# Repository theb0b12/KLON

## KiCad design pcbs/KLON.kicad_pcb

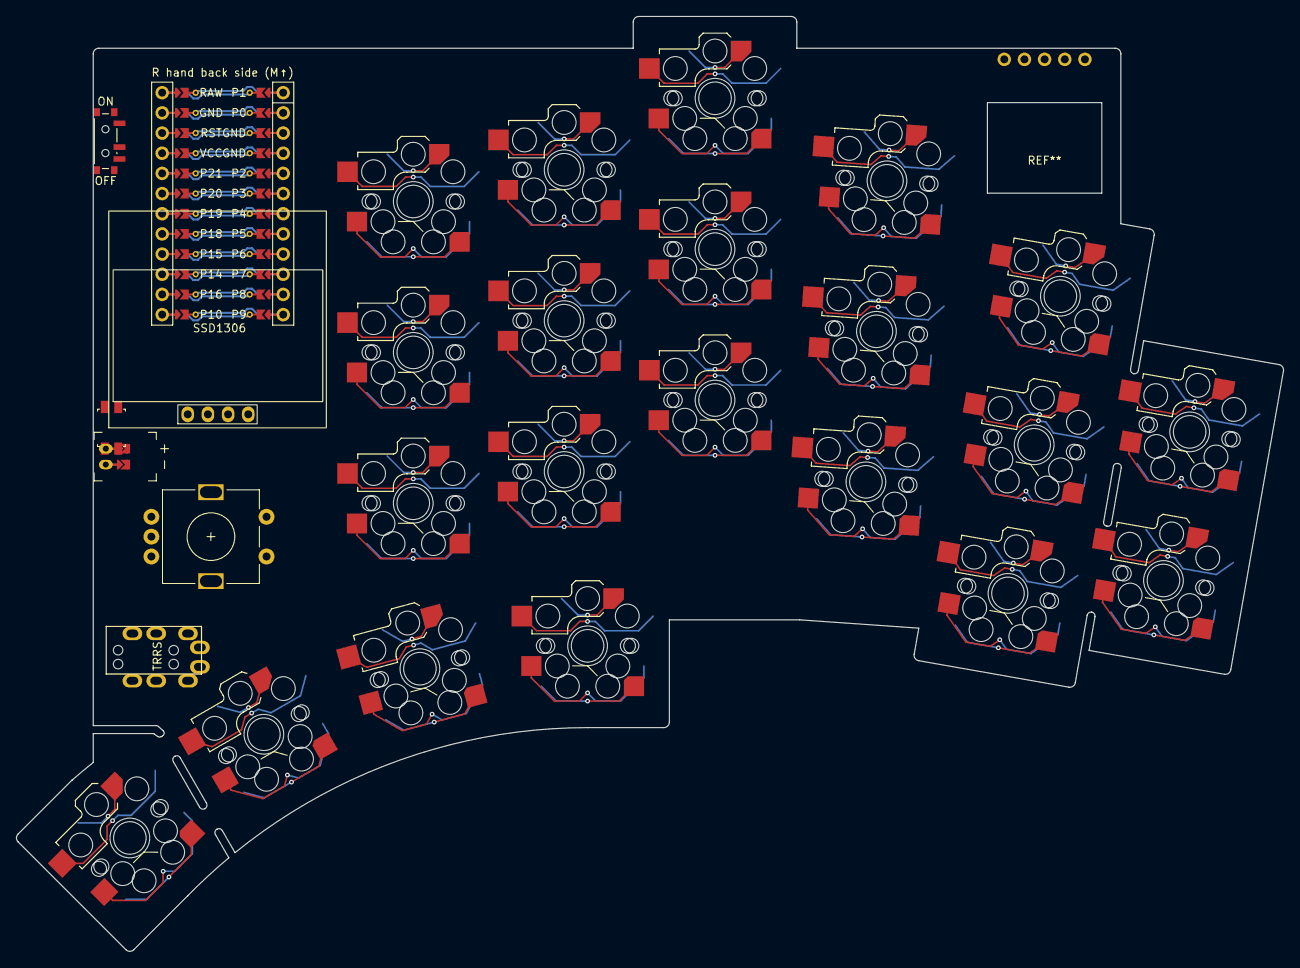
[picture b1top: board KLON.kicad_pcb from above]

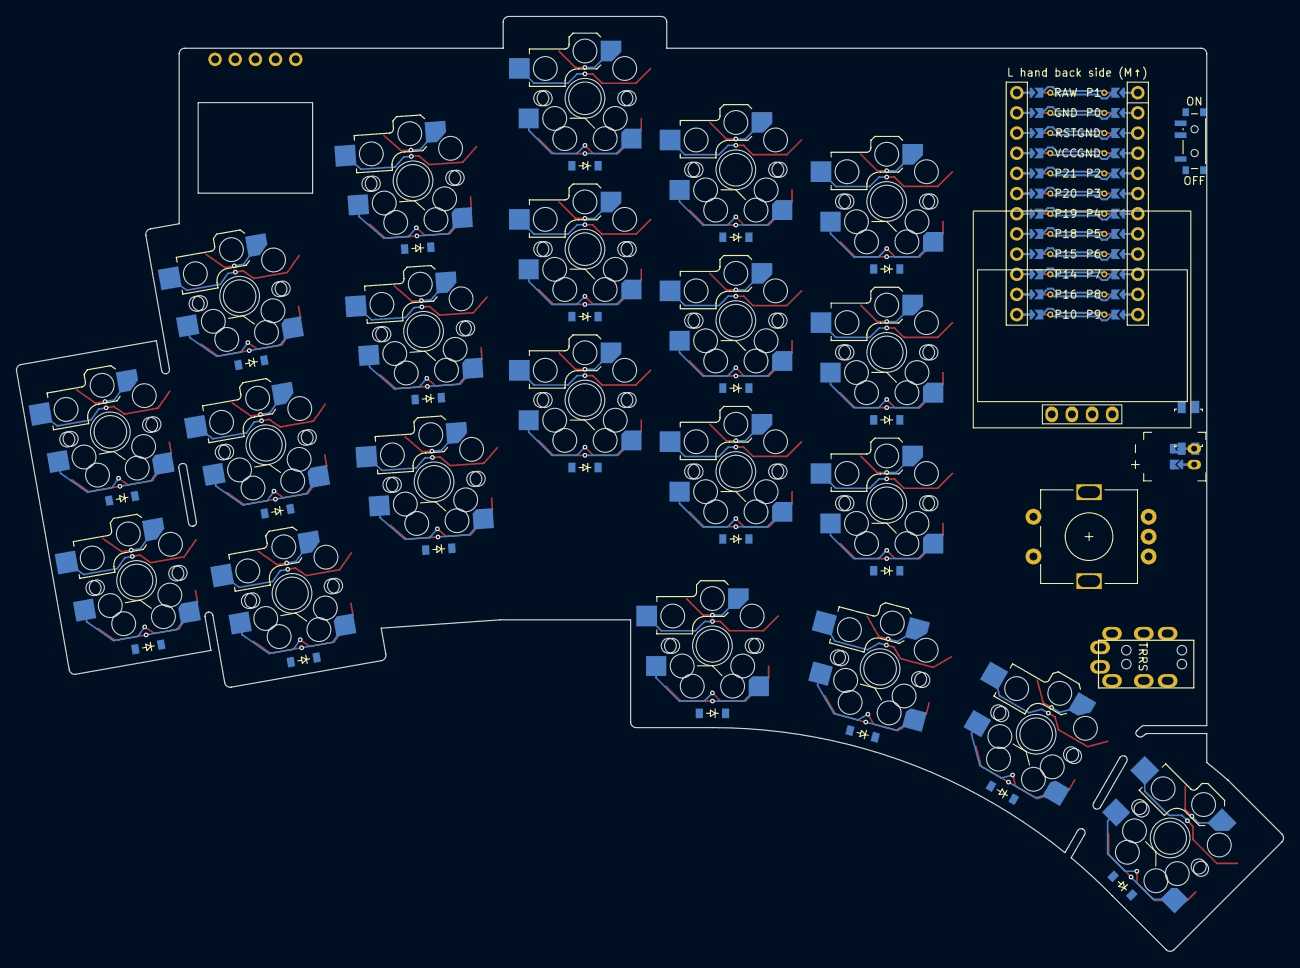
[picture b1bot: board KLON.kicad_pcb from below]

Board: 2 copper layers, 159.6 x 117.7 mm, 71 parts (63 on the bottom side), 29 nets.

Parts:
D1, D2, D3, D4, D5, D6, D7, D8, D9, D10, D11, D12, D13, D14, D15, D16, D17, D18, D19, D20, D21: diode_tht_sod123
JST1: battery_connector_jst_ph_2
MCU1: mcu_nice_nano
PWR1: power_switch_smd_side
RST1: reset_switch_smd_side
S1, S2, S3, S4, S5, S6, S7, S8, S9, S10, S11, S12, S13, S14, S15, S16, S17, S18, S19, S20, S21: switch_choc_v1_v2
S22, S23, S24, S25, S26, S27, S28, S29, S30, S31, S32, S33, S34, S35, S36, S37, S38, S39, S40, S41, S42: switch_mx
XX1: Pimoroni Haptic Buzz DRV2605L Driver
XX2: RotaryEncoder_Alps_EC11E-Switch_Vertical_H20mm-keebio_modif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
XX3: SSD1306_128x64OLED
XX4: MJ-4PP-9

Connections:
1_r0: D18.2, S18.2, S39.2
2_r0: D19.2, S19.2, S40.2
3_r0: D20.2, S20.2, S41.2
4_r0: D21.2, S21.2, S42.2
BAT_P: JST1.1, PWR1.1, PWR1.3
GND: JST1.2, MCU1.103, MCU1.104, MCU1.123, RST1.1, RST1.3
JST1_1: JST1.11, JST1.21, JST1.31
JST1_2: JST1.12, JST1.22, JST1.32
RAW: MCU1.124, PWR1.2
RST: MCU1.122, RST1.2, RST1.4
idk: XX2.A, XX2.B, XX2.C, XX2.MP, XX2.S1, XX2.S2
index_bottom: D4.2, S4.2, S25.2
index_home: D5.2, S5.2, S26.2
index_top: D6.2, S6.2, S27.2
inner_bottom: D1.2, S1.2, S22.2
inner_home: D2.2, S2.2, S23.2
inner_top: D3.2, S3.2, S24.2
middle_bottom: D7.2, S7.2, S28.2
middle_home: D8.2, S8.2, S29.2
middle_top: D9.2, S9.2, S30.2
pinky_bottom: D13.2, S13.2, S34.2
pinky_extra_bottom: D16.2, S16.2, S37.2
pinky_extra_home: D17.2, S17.2, S38.2
pinky_home: D14.2, S14.2, S35.2
pinky_top: D15.2, S15.2, S36.2
ring_bottom: D10.2, S10.2, S31.2
ring_home: D11.2, S11.2, S32.2
ring_top: D12.2, S12.2, S33.2
undefined: XX1.1, XX1.2, XX1.3, XX1.4, XX1.5, XX3.1, XX3.2, XX3.3, XX3.4, XX4.1, XX4.2, XX4.3, XX4.4

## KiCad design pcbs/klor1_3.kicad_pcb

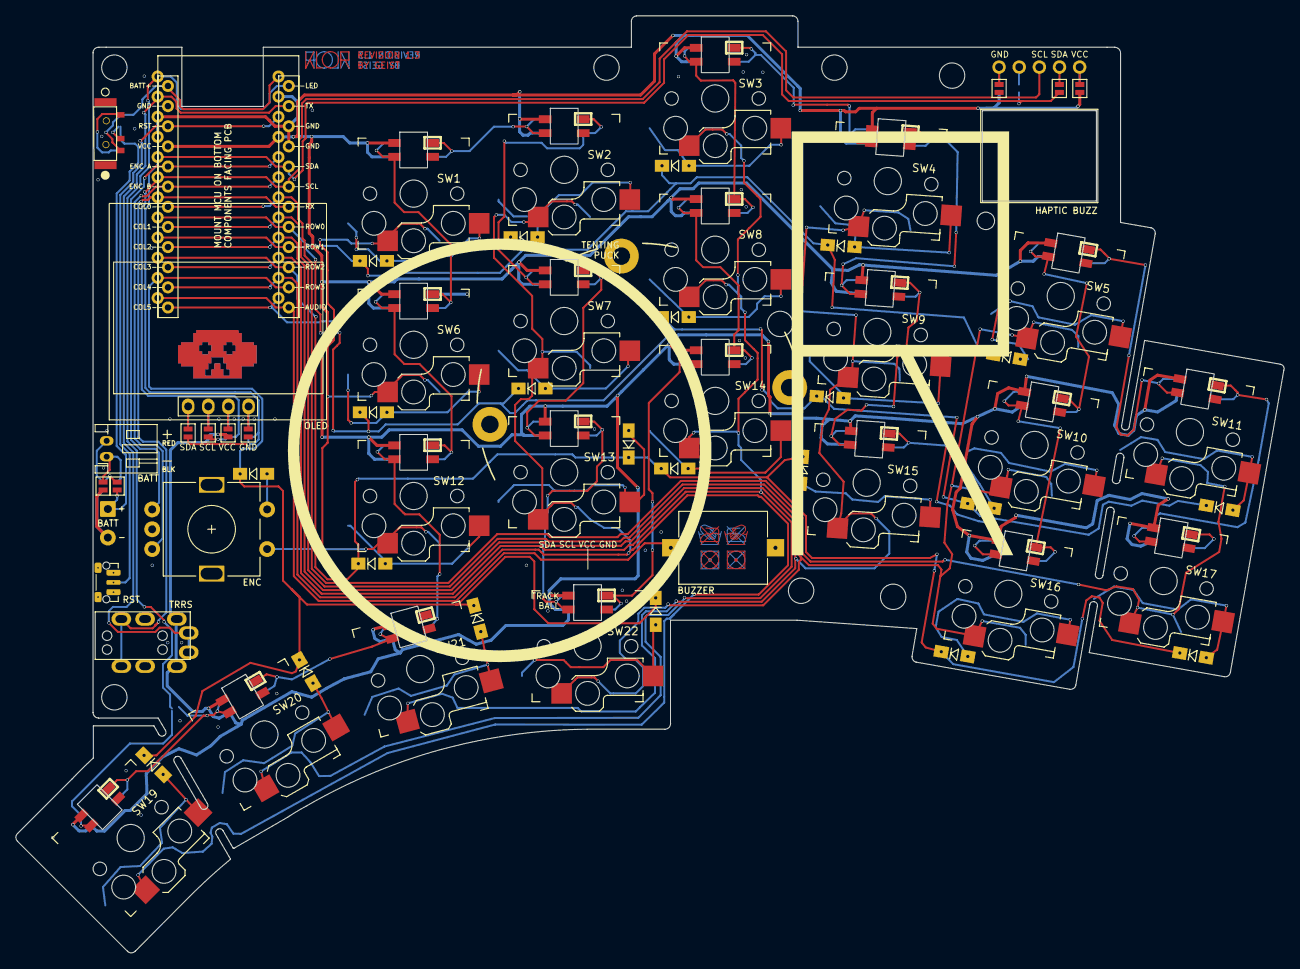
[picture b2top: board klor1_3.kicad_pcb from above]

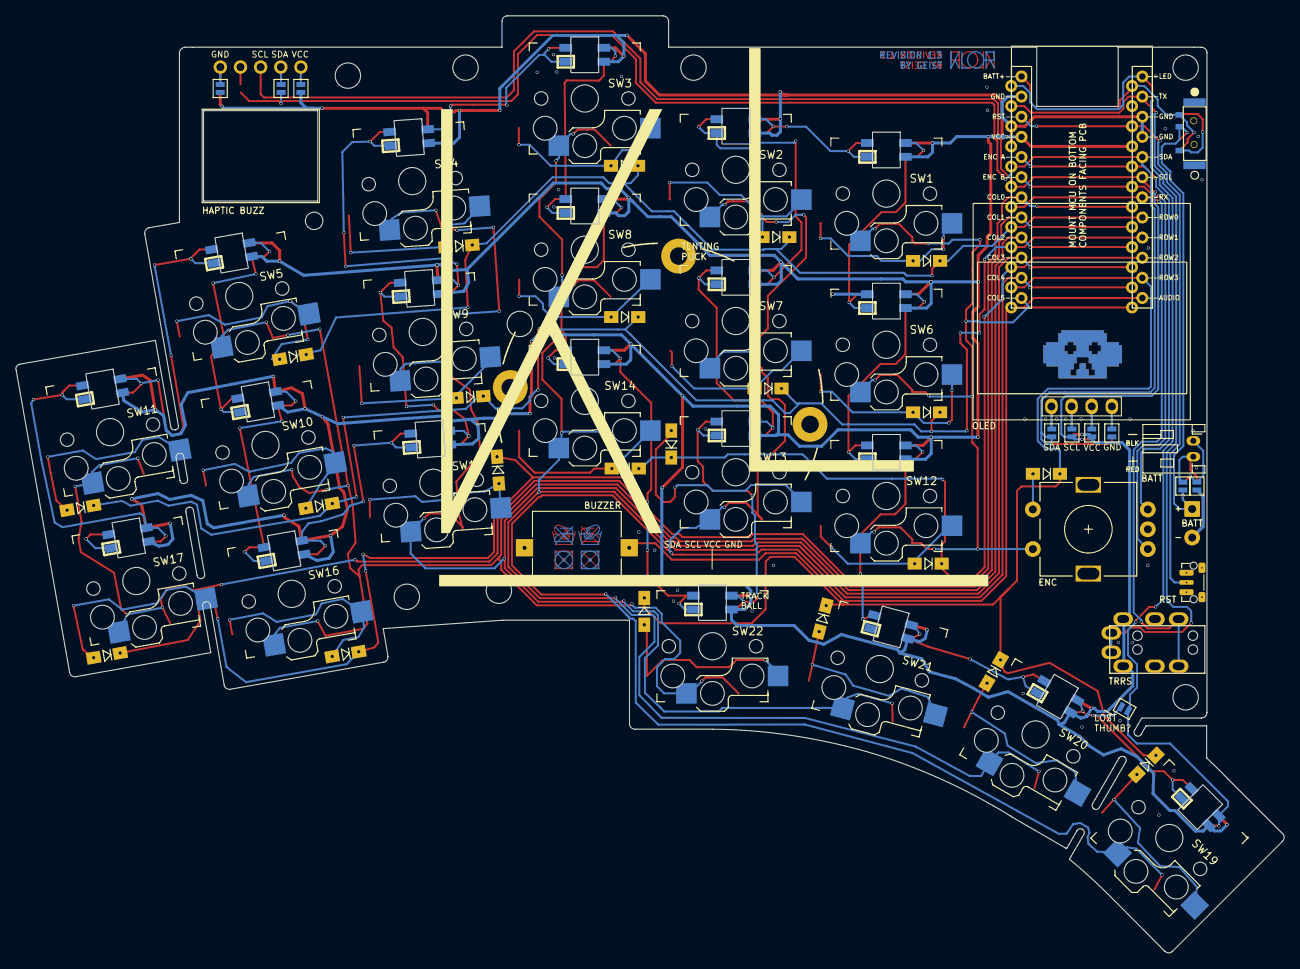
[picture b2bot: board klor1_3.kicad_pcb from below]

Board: 2 copper layers, 160.0 x 118.2 mm, 81 parts (11 on the bottom side), 75 nets.

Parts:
BT1: JST Connector; JST_PH_reversible
BT2: Battery_Cell; custombatteryconnector_small
BZ1: Buzzer; Buzzer_Mallory_AST1109MLTRQ_reversible
D1, D2, D3, D4, D5, D6, D7, D8, D9, D10, D11, D12, D13, D14, D15, D16, D17, D18, D19, D20, D21, D22: D_Small; Diode_SOD123
J1: MJ-4PP-9
J2: Haptic Buzz; Pimoroni Haptic Buzz DRV2605L Driver
JP1, JP2, JP3, JP4, JP5, JP6, JP7, JP8, JP22, JP23, JP24, JP25, JP26, JP27, JP28: Device_Jumper_NO_Small; Jumper
JP12, JP14: VCC Jumper; Jumper
JP13, JP15: GND Jumper; Jumper
MH1, MH2, MH3, MH4, MH5, MH6, MH7, MH8: MountingHole_3.2mm_M3
MH9: MountingHole_2.2mm_M2
OLED1: SSD1306; SSD1306_128x64OLED
PSW1: SW_DPDT_x2; MSK12C02_reversible
RSW1: SW_Push; SW_Push_1P1T-MP_NO_Horizontal_Alps_SKRTLAE010_both_sides
SW1, SW2, SW3, SW4, SW5, SW6, SW7, SW8, SW9, SW10, SW11, SW12, SW13, SW14, SW15, SW16, SW17, SW19, SW20, SW21, SW22: SW_PUSH-MX_W_LED; Kailh_socket_PG1350_reversible_with_sk6812_mini
SW18: RotaryEncoder_Switch; RotaryEncoder_Alps_EC11E-Switch_Vertical_H20mm-keebio_modif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
U1: ProMicro

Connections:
+BATT: PSW1.3 (C), U1.24 (RAW)
/PAD1: BT1.1 (+), JP22.1, JP23.1
/PAD2: BT1.2 (-), JP24.1, JP25.1
/PSW: BT2.1 (+), JP23.2, JP24.2, PSW1.2 (B)
AUDIO: BZ1.1 (-), U1.12 (9/B5)
ENCA: SW18.A, U1.20 (F4/A3)
ENCB: SW18.B, U1.19 (F5/A2)
GND: BT2.2 (-), BZ1.2 (+), J1.2, JP1.2, JP8.2, JP13.1 (A), JP15.1 (A), JP22.2, JP25.2, RSW1.1, SW1.2 (VSS), SW2.2 (VSS), SW3.2 (VSS), SW4.2 (VSS), SW5.2 (VSS), SW6.2 (VSS), SW7.2 (VSS), SW8.2 (VSS), SW9.2 (VSS), SW10.2 (VSS), SW11.2 (VSS), SW12.2 (VSS), SW13.2 (VSS), SW14.2 (VSS), SW15.2 (VSS), SW16.2 (VSS), SW17.2 (VSS), SW18.C, SW19.2 (VSS), SW20.2 (VSS), SW21.2 (VSS), SW22.2 (VSS), U1.3 (GND), U1.4 (GND), U1.23 (GND)
LED: JP26.2, SW19.3 (DIN), U1.1 (TX0/D3)
unnamed: D1.2 (A), SW1.6
unnamed: D2.2 (A), SW2.6
unnamed: D3.2 (A), SW3.6
unnamed: D4.2 (A), SW4.6
unnamed: D5.2 (A), SW5.6
unnamed: D6.2 (A), SW6.6
unnamed: D7.2 (A), SW7.6
unnamed: D8.2 (A), SW8.6
unnamed: D9.2 (A), SW9.6
unnamed: D10.2 (A), SW10.6
unnamed: D11.2 (A), SW11.6
unnamed: D12.2 (A), SW12.6
unnamed: D13.2 (A), SW13.6
unnamed: D14.2 (A), SW14.6
unnamed: D15.2 (A), SW15.6
unnamed: D16.2 (A), SW16.6
unnamed: D17.2 (A), SW17.6
unnamed: D19.2 (A), SW19.6
unnamed: D20.2 (A), SW20.6
unnamed: D21.2 (A), SW21.6
unnamed: D22.2 (A), SW22.6
unnamed: J2.1, JP12.2 (B), JP13.2 (B)
unnamed: J2.2, JP27.2
unnamed: J2.4, JP28.2
unnamed: J2.5, JP14.2 (B), JP15.2 (B)
unnamed: JP1.1, JP5.1, OLED1.1 (GND)
unnamed: JP2.1, JP6.1, OLED1.2 (VCC)
unnamed: JP3.1, JP7.1, OLED1.3 (SCL)
unnamed: JP4.1, JP8.1, OLED1.4 (SDA)
unnamed: JP26.1, SW19.1 (DOUT), SW20.3 (DIN)
unnamed: SW1.1 (DOUT), SW2.3 (DIN)
unnamed: SW1.3 (DIN), SW6.1 (DOUT)
unnamed: SW2.1 (DOUT), SW7.3 (DIN)
unnamed: SW3.1 (DOUT), SW4.3 (DIN)
unnamed: SW3.3 (DIN), SW8.1 (DOUT)
unnamed: SW4.1 (DOUT), SW9.3 (DIN)
unnamed: SW5.3 (DIN), SW10.1 (DOUT)
unnamed: SW10.3 (DIN), SW16.1 (DOUT)
unnamed: SW11.1 (DOUT), SW17.3 (DIN)
unnamed: SW5.1 (DOUT), SW11.3 (DIN)
unnamed: SW6.3 (DIN), SW12.1 (DOUT)
unnamed: SW12.3 (DIN), SW21.1 (DOUT)
unnamed: SW13.1 (DOUT), SW22.3 (DIN)
unnamed: SW7.1 (DOUT), SW13.3 (DIN)
unnamed: SW8.3 (DIN), SW14.1 (DOUT)
unnamed: SW14.3 (DIN), SW22.1 (DOUT)
unnamed: SW15.1 (DOUT), SW16.3 (DIN)
unnamed: SW9.1 (DOUT), SW15.3 (DIN)
unnamed: SW20.1 (DOUT), SW21.3 (DIN)
RESET: RSW1.2, U1.22 (RST)
RX: J1.3, U1.7 (4/D4)
SCL: J2.3, JP3.2, JP6.2, U1.6 (3/D0/SCL)
SDA: JP4.2, JP5.2, JP27.1, JP28.1, U1.5 (2/D1/SDA)
SW18A: SW1.5, SW6.5, SW12.5, SW18.S1, U1.13 (B6/10)
SW18B: D18.2 (A), SW18.S2
TX: J1.4, U1.2 (RX1/D2)
VCC: J1.1, JP2.2, JP7.2, JP12.1 (A), JP14.1 (A), SW1.4 (VDD), SW2.4 (VDD), SW3.4 (VDD), SW4.4 (VDD), SW5.4 (VDD), SW6.4 (VDD), SW7.4 (VDD), SW8.4 (VDD), SW9.4 (VDD), SW10.4 (VDD), SW11.4 (VDD), SW12.4 (VDD), SW13.4 (VDD), SW14.4 (VDD), SW15.4 (VDD), SW16.4 (VDD), SW17.4 (VDD), SW19.4 (VDD), SW20.4 (VDD), SW21.4 (VDD), SW22.4 (VDD), U1.21 (VCC)
col0: SW11.5, SW17.5, U1.18 (F6/A1)
col1: SW5.5, SW10.5, SW16.5, SW22.5, U1.17 (F7/A0)
col2: SW4.5, SW9.5, SW15.5, SW21.5, U1.16 (B1/15)
col3: SW3.5, SW8.5, SW14.5, SW20.5, U1.15 (B3/14)
col4: SW2.5, SW7.5, SW13.5, SW19.5, U1.14 (B2/16)
row0: D1.1 (K), D2.1 (K), D3.1 (K), D4.1 (K), D5.1 (K), U1.8 (5/C6)
row1: D6.1 (K), D7.1 (K), D8.1 (K), D9.1 (K), D10.1 (K), D11.1 (K), U1.9 (6/D7)
row2: D12.1 (K), D13.1 (K), D14.1 (K), D15.1 (K), D16.1 (K), D17.1 (K), U1.10 (7/E6)
row3: D18.1 (K), D19.1 (K), D20.1 (K), D21.1 (K), D22.1 (K), U1.11 (8/B4)
